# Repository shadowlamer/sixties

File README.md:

# sixties
Electronic postcard based on STM32 and SPI LCD

[See hardware on EasyEDA](https://easyeda.com/shadowlamer/sixties)

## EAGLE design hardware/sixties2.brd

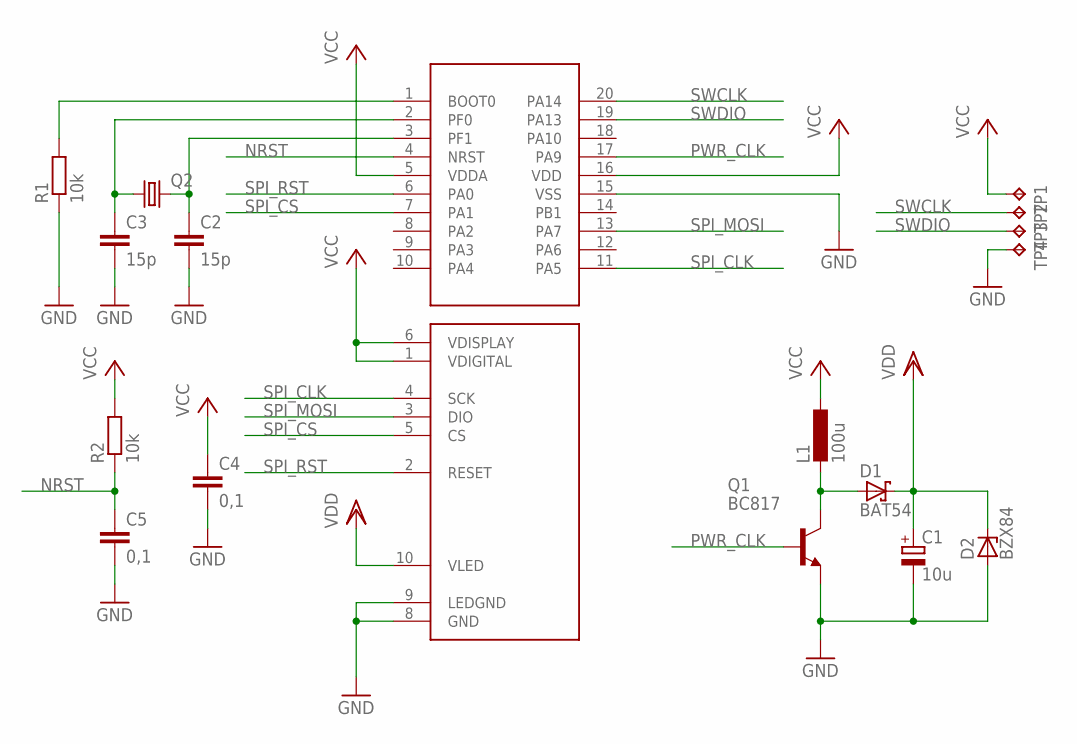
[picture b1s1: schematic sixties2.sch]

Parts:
C1: 10u; D/7343-31W
C2, C3: 15p; C0805K
C4, C5: 0,1; C0805K
D1: BAT54; SOT23
D2: BZX84; TO236
L1: 100u; L1812
Q1: BC817; SOT23-BEC
Q2: CRYSTALSM49; SM49
R1, R2: 10k; M0805
TP1, TP2, TP3, TP4: TPTP11R; TP11R
U1: STM32F030F4; TSSOP20
U$2: NOKIA6100_LCD

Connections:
GND: C1.-, C2.2, C3.2, C4.2, C5.2, D2.A, Q1.E, R1.1, TP4.TP, U1.15 (VSS), U$2.8 (GND), U$2.9 (LEDGND)
unnamed: D1.1 (A), L1.2, Q1.C
unnamed: C3.1, Q2.1, U1.2 (PF0)
unnamed: C2.1, Q2.2, U1.3 (PF1)
unnamed: R1.2, U1.1 (BOOT0)
NRST: C5.1, R2.1, U1.4 (NRST)
PWR_CLK: Q1.B, U1.17 (PA9)
SPI_CLK: U1.11 (PA5), U$2.4 (SCK)
SPI_CS: U1.7 (PA1), U$2.5 (CS)
SPI_MOSI: U1.13 (PA7), U$2.3 (DIO)
SPI_RST: U1.6 (PA0), U$2.2 (RESET)
SWCLK: TP2.TP, U1.20 (PA14)
SWDIO: TP3.TP, U1.19 (PA13)
VCC: C4.1, L1.1, R2.2, TP1.TP, U1.5 (VDDA), U1.16 (VDD), U$2.1 (VDIGITAL), U$2.6 (VDISPLAY)
VDD: C1.+, D1.3 (C), D2.C, U$2.10 (VLED)

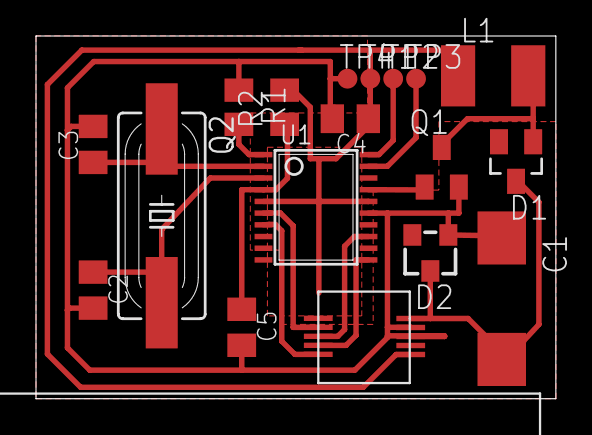
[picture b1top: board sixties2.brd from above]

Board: 2 copper layers, 28.9 x 20.2 mm, 18 parts (0 on the bottom side), 15 nets.

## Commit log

2016-01-03 :tada: Added .gitattributes & .gitignore files
2016-01-03 Initial import
2016-01-03 Schematic and PCB files added.
